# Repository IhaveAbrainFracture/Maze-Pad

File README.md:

# Maze-Pad made by @TheVirtuoso on slack, Vikas IRL
A general spin on a macro-pad, with a fully customised case, PCB, and Firmware. It should also be fully assemblable and useable less than 20 mins after getting everything. Big thanks to Hack Club (Highway) and PCBway for helping me make this

Here is the full cad model to view before you download anything or want a deeper look
https://cad.onshape.com/documents/6287fe38e10122eb28751222/w/de1210ab97eae6cc3d55f10b/e/6d662cd5a03a31552cd37cf9?renderMode=0&uiState=6871c3cb6e1d2f4d0885fcee

# sob story/ why im making this
im a broke highschool student while simultaniously being the youngest in my family often what this mean is all  (if not most) of the technology i own is either a hand-me-down, something i bought myself or something i 'borrowed without the intention of returning' to prove this point want to guess what my current keyboard and mouse look like? Wrong its one of those chunky school keyboard and mice combos that your school bulk buys for there comp room. aside i rly needed an upgrade so i decide to stop being a lazy and work on something. further down the line i also plan on making a keyboard so i kind of treated this as a 'test' run so i could learn the ropes and all

# Specification /cool gimicks (software)
- fully custom code (ie i didnt just yoink the hackpad guide code and make some tweaks)
- 4 macros ( Copy,Paste,Save and alt tab)
- 2 light control buttons ( change in colour, change in pattern)
- 1 layer (I plan on making this 2 layer or more in the future)

 # Specification /cool gimicks (Electronics)
  - wired in a 2x3 matrix
  - custom pcb with funni silk image
  - 2 leds (Neo pixels) which are poorly spaced apart
  - Hopefully smd mounted Xiao
  - diodes at the back
  - 

# Specification /cool gimicks (Mechanical)
- fully custom case which doesnt require screws, Bolts or glue (i designed the case based on cool woodworking stuff)
- 7 fully custom mazes for your ADHD
- Custom Maze themed keycaps

- Groves on the side
- maximum fillets
- high mounted cover (this is on purpose i swear, its so it fits my stuff)
- crude hole to look over your enslaved xiao
- backlighting
- funni logos and names
- its black, and white

# instruction to build
ngl if ur building this ur either chonicaly lazy or are collecting hackpads liek infinity stones cos like it cannot be that hard to build your ow. *Aside*
1. plug in your xiao and hold the boot button (clickty clackity on the right) then move the entire firmware folder into the xiao
2. assemble the easy stuff ie the keycaps and put them of the switches
3. place the pcb and all soldered part attacked to it into the main bases (the chunky 3D print)
5. in the allocated slot add the side connector thing thats white and the other white part, for the small bridge if u want the random logoing i put use that side if not rotate it 180 and place it
6. place the case lid and test
7. place small bearing balls into all the mazes
8. done

# bill of mats

| Item | Ammount |From where|
| ------------- | ------------- |----------|
|  mx switches x6  |  |from hackpad kit (i need one of the kits btw)|
|Seeed XIAO RP2040 x1 ||("")|
|SK6812 MINI-E LEDs x2 ||("")|
|3D Printing| none|Printing legion|
|PCB|??$|PCBWAY, Im getting sponsered :D < |
|Solder Iron|??|???|
|Flux|$1.53|"https://www.aliexpress.com/item/1005008783332875.html?spm=a2g0o.productlist.main.15.eab81f2bCFhjVT&algo_pvid=45cc1b00-6bcf-43ca-b888-5c4e79205a33&algo_exp_id=45cc1b00-6bcf-43ca-b888-5c4e79205a33-14&pdp_ext_f=%7B"order"%3A"231"%2C"eval"%3A"1"%7D&pdp_npi=4%40dis%21AUD%217.41%211.53%21%21%2134.52%217.16%21%40212e508d17522305550312149ef5c6%2112000046648707772%21sea%21AU%210%21ABX&curPageLogUid=8c35HYaTwcCc&utparam-url=scene%3Asearch%7Cquery_from%3A"|
|Solder|$1.53| https://www.aliexpress.com/item/1005007703287757.html?spm=a2g0o.productlist.main.12.65f06325LWNWpv&algo_pvid=0f0b2a51-30e8-41ca-9b4d-5341719839aa&algo_exp_id=0f0b2a51-30e8-41ca-9b4d-5341719839aa-11&pdp_ext_f=%7B"order"%3A"3030"%2C"eval"%3A"1"%7D&pdp_npi=4%40dis%21AUD%216.45%211.53%21%21%2130.03%217.13%21%400b1bf20817522311015765496e776c%2112000041915671265%21sea%21AU%210%21ABX&curPageLogUid=g3sCp5CWQzIl&utparam-url=scene%3Asearch%7Cquery_from%3A|

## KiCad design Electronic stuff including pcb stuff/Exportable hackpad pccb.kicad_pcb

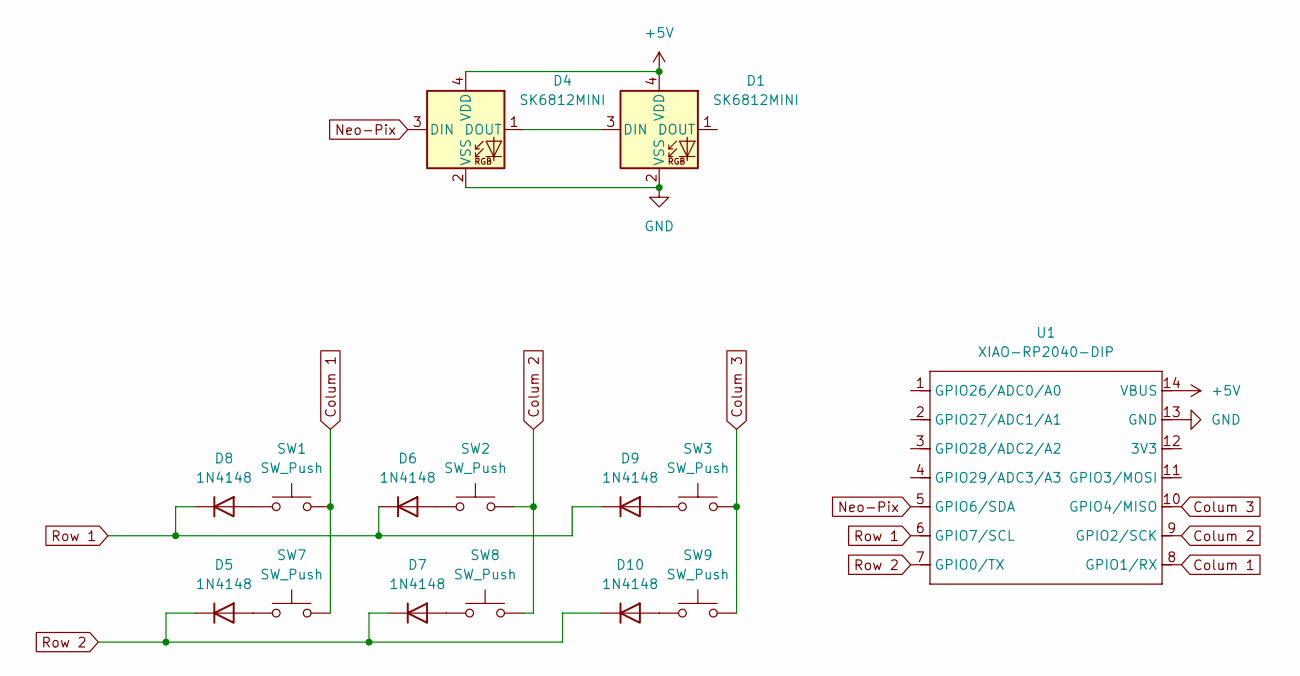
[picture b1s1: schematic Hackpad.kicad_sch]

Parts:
D1, D4: SK6812MINI; LED_SK6812MINI_PLCC4_3.5x3.5mm_P1.75mm
D5, D6, D7, D8, D9, D10: 1N4148; D_DO-35_SOD27_P7.62mm_Horizontal
SW1, SW2, SW3, SW7, SW8, SW9: SW_Push; SW_Cherry_MX_1.00u_PCB
U1: XIAO-RP2040-DIP

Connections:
+5V: D1.4 (VDD), D4.4 (VDD), U1.14 (VBUS)
Colum 1: SW1.2, SW7.2, U1.8 (GPIO1/RX)
Colum 2: SW2.2, SW8.2, U1.9 (GPIO2/SCK)
Colum 3: SW3.2, SW9.2, U1.10 (GPIO4/MISO)
GND: D1.2 (VSS), D4.2 (VSS), U1.13 (GND)
Neo-Pix: D4.3 (DIN), U1.5 (GPIO6/SDA)
unnamed: D1.3 (DIN), D4.1 (DOUT)
unnamed: D5.2 (A), SW7.1
unnamed: D6.2 (A), SW2.1
unnamed: D7.2 (A), SW8.1
unnamed: D8.2 (A), SW1.1
unnamed: D9.2 (A), SW3.1
unnamed: D10.2 (A), SW9.1
Row 1: D6.1 (K), D8.1 (K), D9.1 (K), U1.6 (GPIO7/SCL)
Row 2: D5.1 (K), D7.1 (K), D10.1 (K), U1.7 (GPIO0/TX)

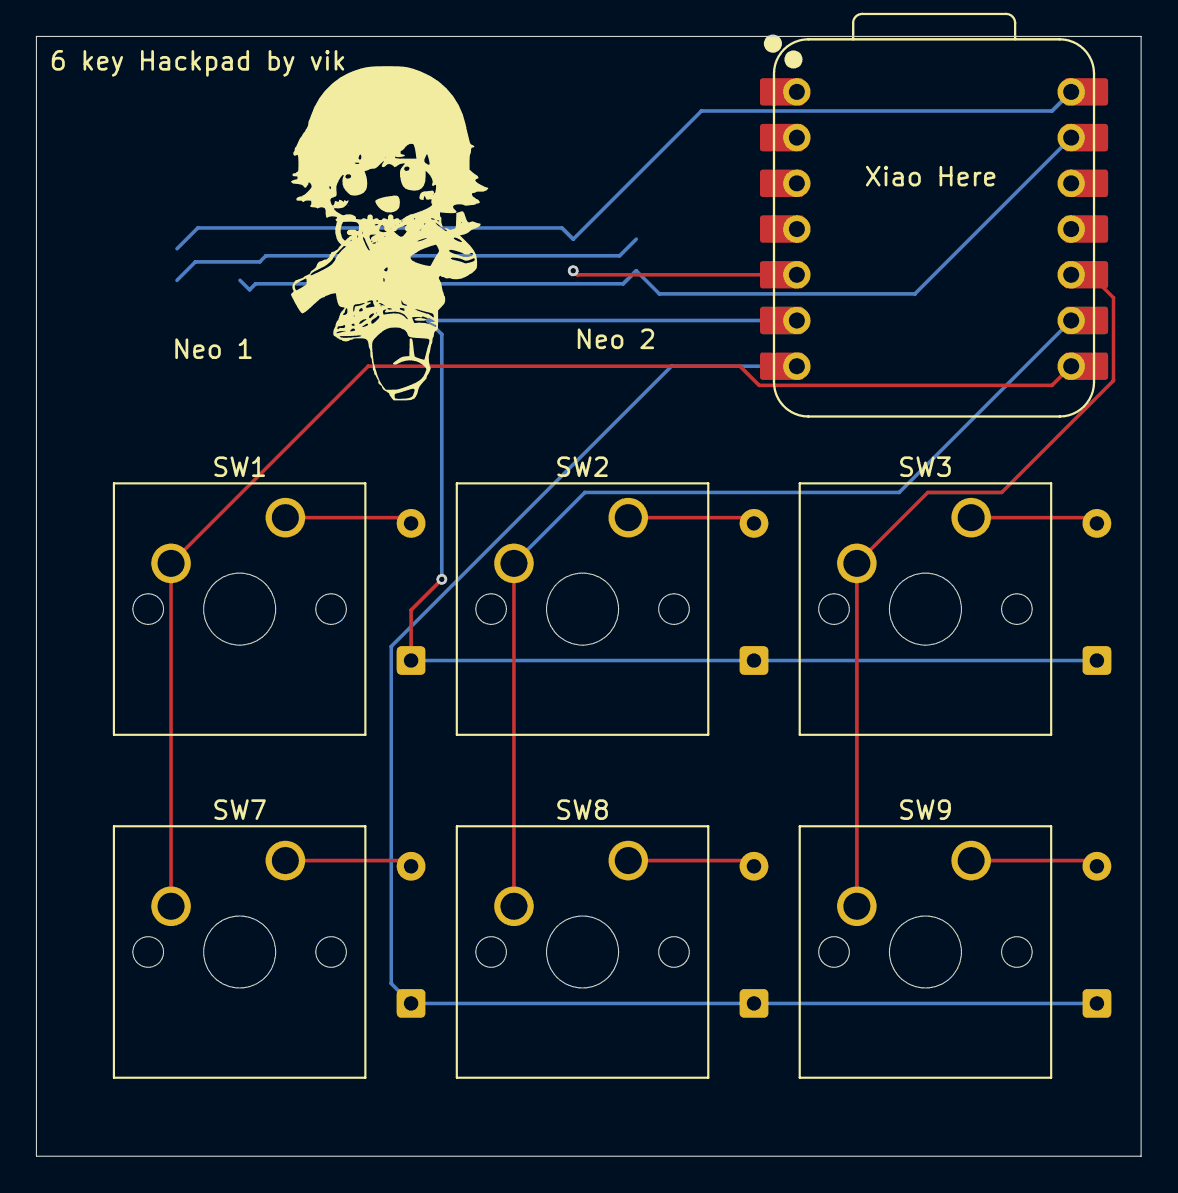
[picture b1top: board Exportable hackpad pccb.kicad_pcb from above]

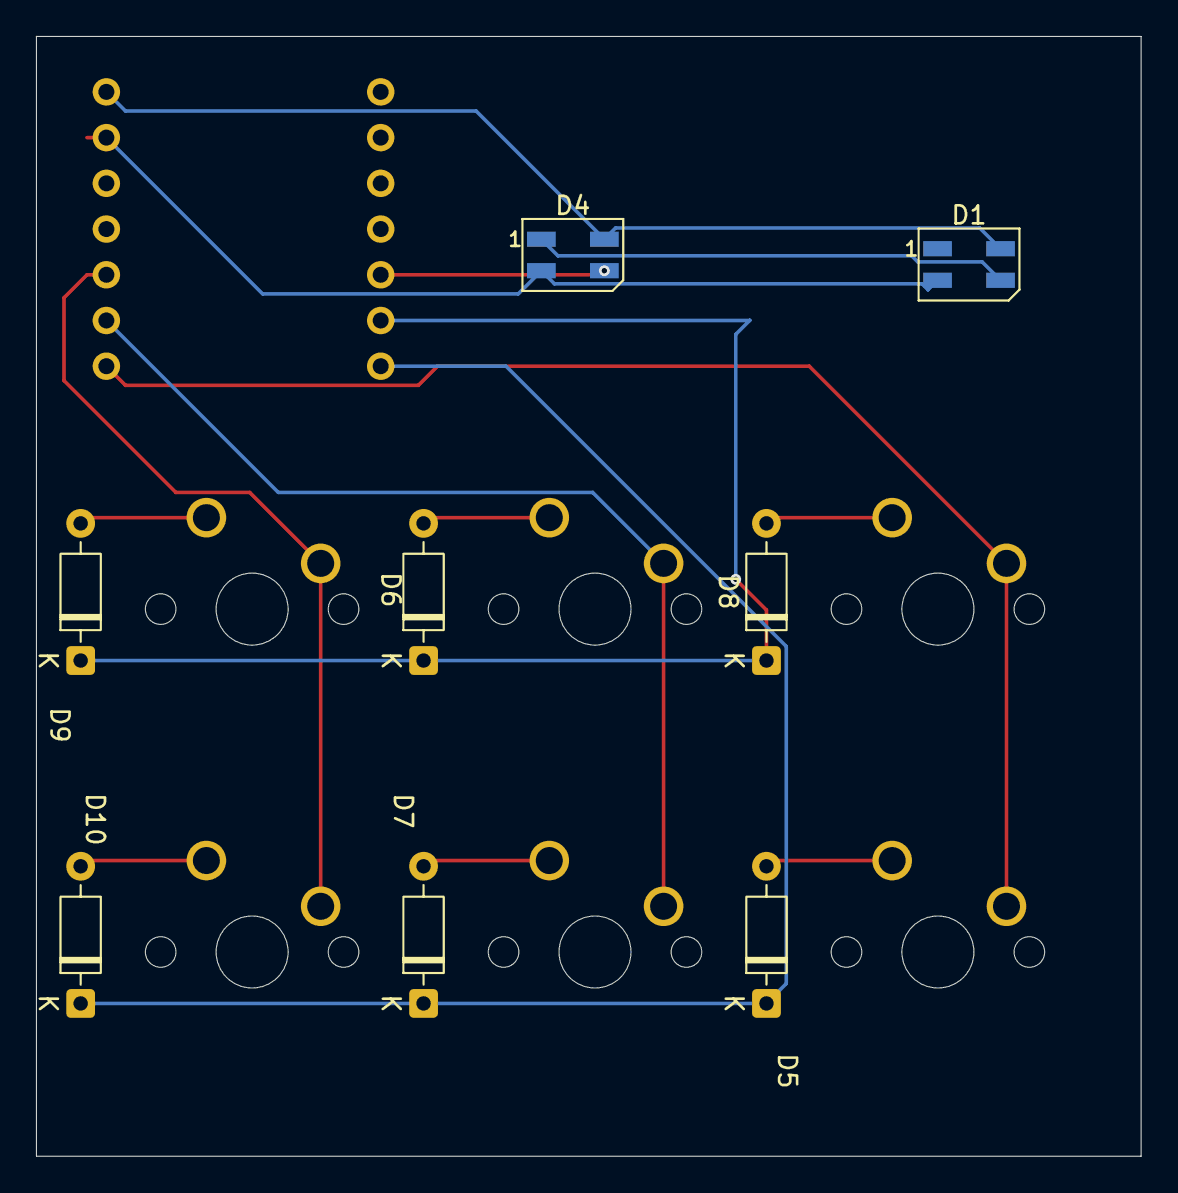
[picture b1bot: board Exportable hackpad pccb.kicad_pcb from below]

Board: 2 copper layers, 61.4 x 62.2 mm, 15 parts (8 on the bottom side), 15 nets.

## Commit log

2025-07-11 Update README.md
    updated the read me
2025-07-11 All the firmware stuff
    god forbid whatever demon possesed to to upload the entire kmk thing
2025-07-11 manufacturing files
    all the files you would need to manufacture the pcb
2025-07-11 Pcb stuff from kicad
2025-07-11 All the 3d prints in STEP
    All of the 3d prints you need to print out, just a note remember to print 6 keycaps
2025-07-11 Uploaded Firmware READ THE DESCRIPTION
    This is all the firmware that you need to put on your xiao aside from the kmk files which can be found somewhere
2025-07-11 Made the journal
    i will be updating this later i need sleep
2025-07-11 update to include slack user and name and onshape link
2025-07-12 fixed readmen stuff
2025-07-12 added photos
2025-07-16 cleaning stuff up
2025-07-16 cleaning up
2025-07-16 files organised
2025-07-18 Update README.md for hq and pcbway
